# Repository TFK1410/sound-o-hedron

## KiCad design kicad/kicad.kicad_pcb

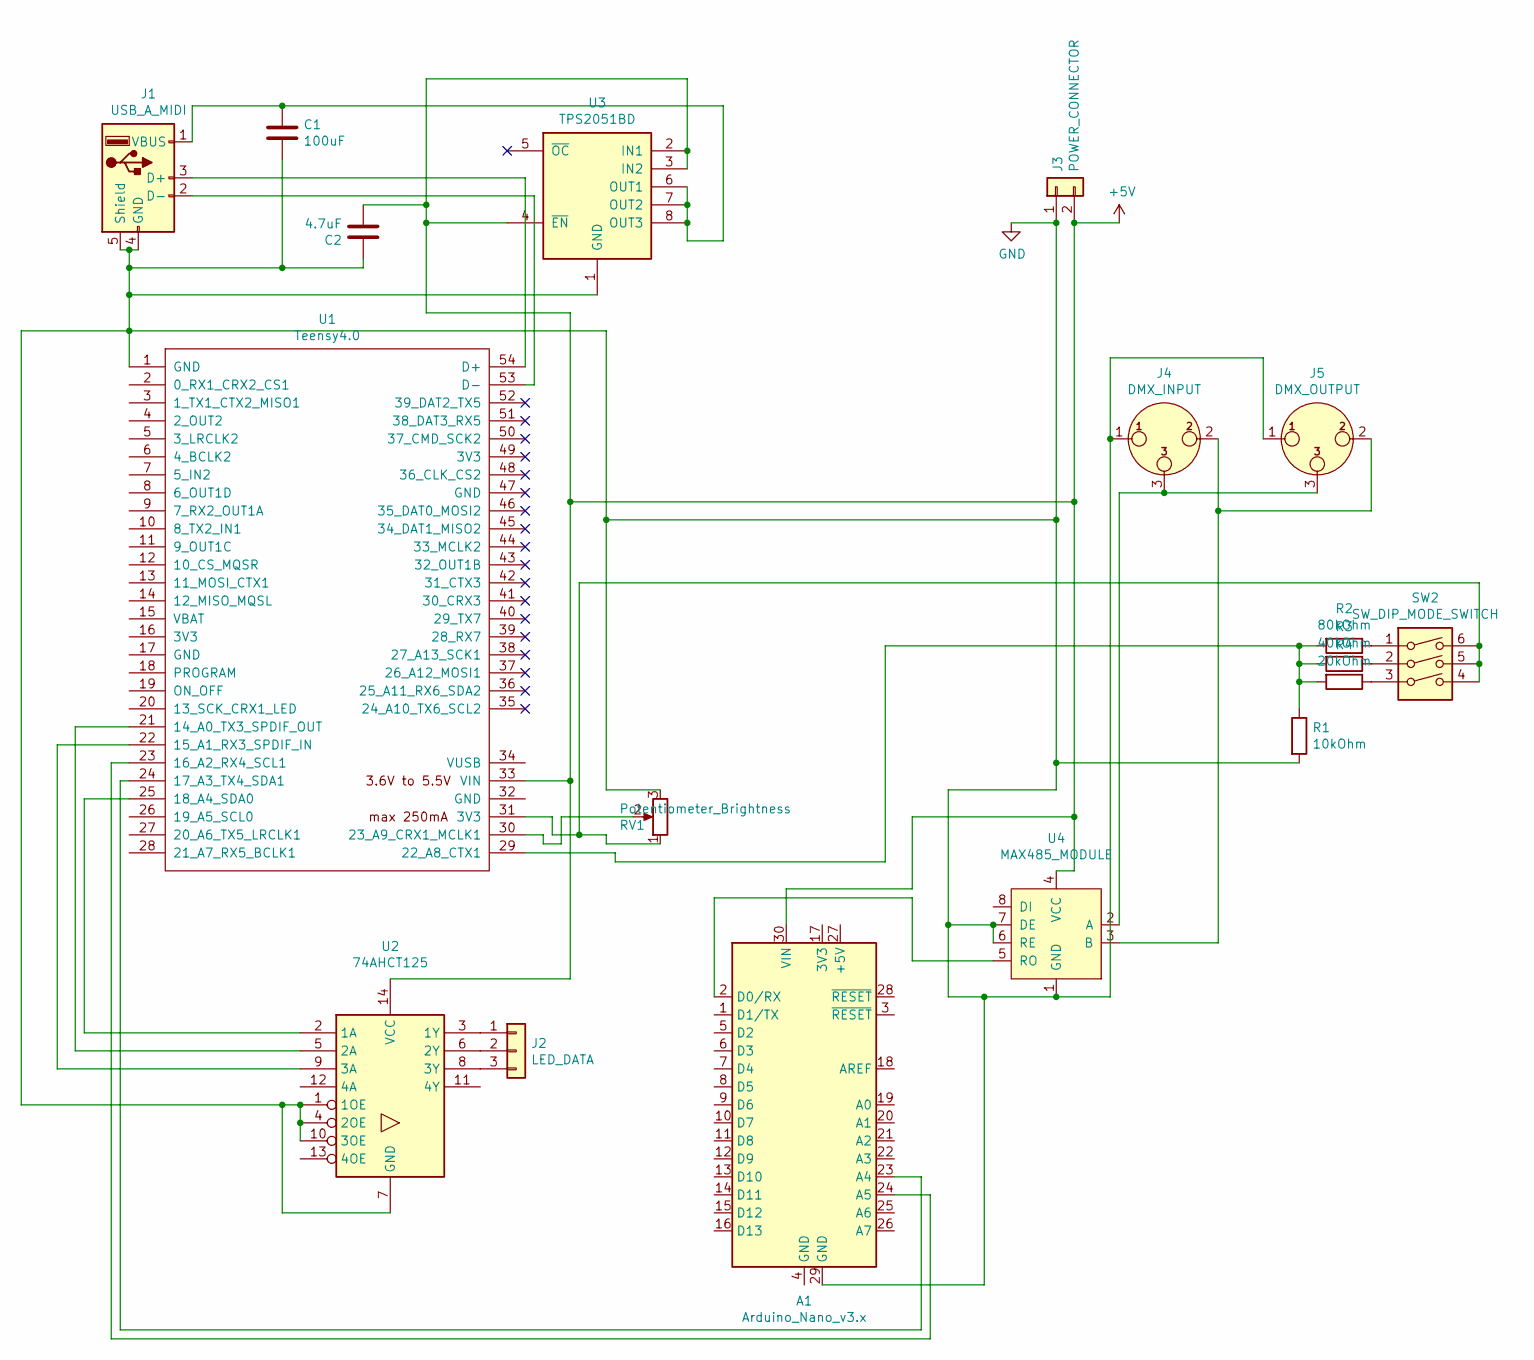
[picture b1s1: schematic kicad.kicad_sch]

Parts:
A1: Arduino_Nano_v3.x; Arduino_Nano
C1: 100uF; CP_Radial_D8.0mm_P3.50mm
C2: 4.7uF; CP_Radial_D5.0mm_P2.00mm
J1: USB_A_MIDI; PinHeader_1x05_P2.54mm_Vertical
J2: LED_DATA; PinHeader_1x03_P2.54mm_Vertical
J3: POWER_CONNECTOR; PinHeader_1x02_P2.54mm_Vertical
J4: DMX_INPUT; PinHeader_1x03_P2.54mm_Vertical
J5: DMX_OUTPUT; PinHeader_1x03_P2.54mm_Vertical
R1: 10kOhm; R_Axial_DIN0207_L6.3mm_D2.5mm_P7.62mm_Horizontal
R2: 80kOhm; R_Axial_DIN0207_L6.3mm_D2.5mm_P7.62mm_Horizontal
R3: 40kOhm; R_Axial_DIN0207_L6.3mm_D2.5mm_P7.62mm_Horizontal
R4: 20kOhm; R_Axial_DIN0207_L6.3mm_D2.5mm_P7.62mm_Horizontal
RV1: Potentiometer_Brightness; PinHeader_1x03_P2.54mm_Vertical
SW2: SW_DIP_MODE_SWITCH; PinHeader_2x03_P2.54mm_Vertical
U1: Teensy4.0; Teensy40_SMT
U2: 74AHCT125; SOIC-14_3.9x8.7mm_P1.27mm
U3: TPS2051BD; SOIC-8_3.9x4.9mm_P1.27mm
U4: MAX485_MODULE; DIP-8_MAX485_MODULE

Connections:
+5V: A1.30 (VIN), C2.1, J3.2, U1.33 (VIN), U2.14 (VCC), U3.2 (IN1), U3.3 (IN2), U3.4 (~EN), U4.4 (VCC)
GND: A1.29 (GND), C1.2, C2.2, J1.4 (GND), J1.5 (Shield), J3.1, J4.1, J5.1, R1.2, RV1.3, U1.1 (GND), U2.1 (1OE), U2.4 (2OE), U2.7 (GND), U2.10 (3OE), U3.1 (GND), U4.1 (GND), U4.6 (RE), U4.7 (DE)
unnamed: A1.2 (D0/RX), U4.5 (RO)
unnamed: A1.23 (A4), U1.24 (17_A3_TX4_SDA1)
unnamed: A1.24 (A5), U1.23 (16_A2_RX4_SCL1)
unnamed: C1.1, J1.1 (VBUS), U3.6 (OUT1), U3.7 (OUT2), U3.8 (OUT3)
unnamed: J1.2 (D-), U1.53 (D-)
unnamed: J1.3 (D+), U1.54 (D+)
unnamed: J2.1, U2.3 (1Y)
unnamed: J2.2, U2.6 (2Y)
unnamed: J2.3, U2.8 (3Y)
unnamed: J4.2, J5.2, U4.3 (B)
unnamed: J4.3, J5.3, U4.2 (A)
unnamed: R1.1, R2.2, R3.2, R4.2, U1.29 (22_A8_CTX1)
unnamed: R2.1, SW2.1
unnamed: R3.1, SW2.2
unnamed: R4.1, SW2.3
unnamed: RV1.1, SW2.4, SW2.5, SW2.6, U1.31 (3V3)
unnamed: RV1.2, U1.30 (23_A9_CRX1_MCLK1)
unnamed: U1.21 (14_A0_TX3_SPDIF_OUT), U2.5 (2A)
unnamed: U1.22 (15_A1_RX3_SPDIF_IN), U2.9 (3A)
unnamed: U1.25 (18_A4_SDA0), U2.2 (1A)

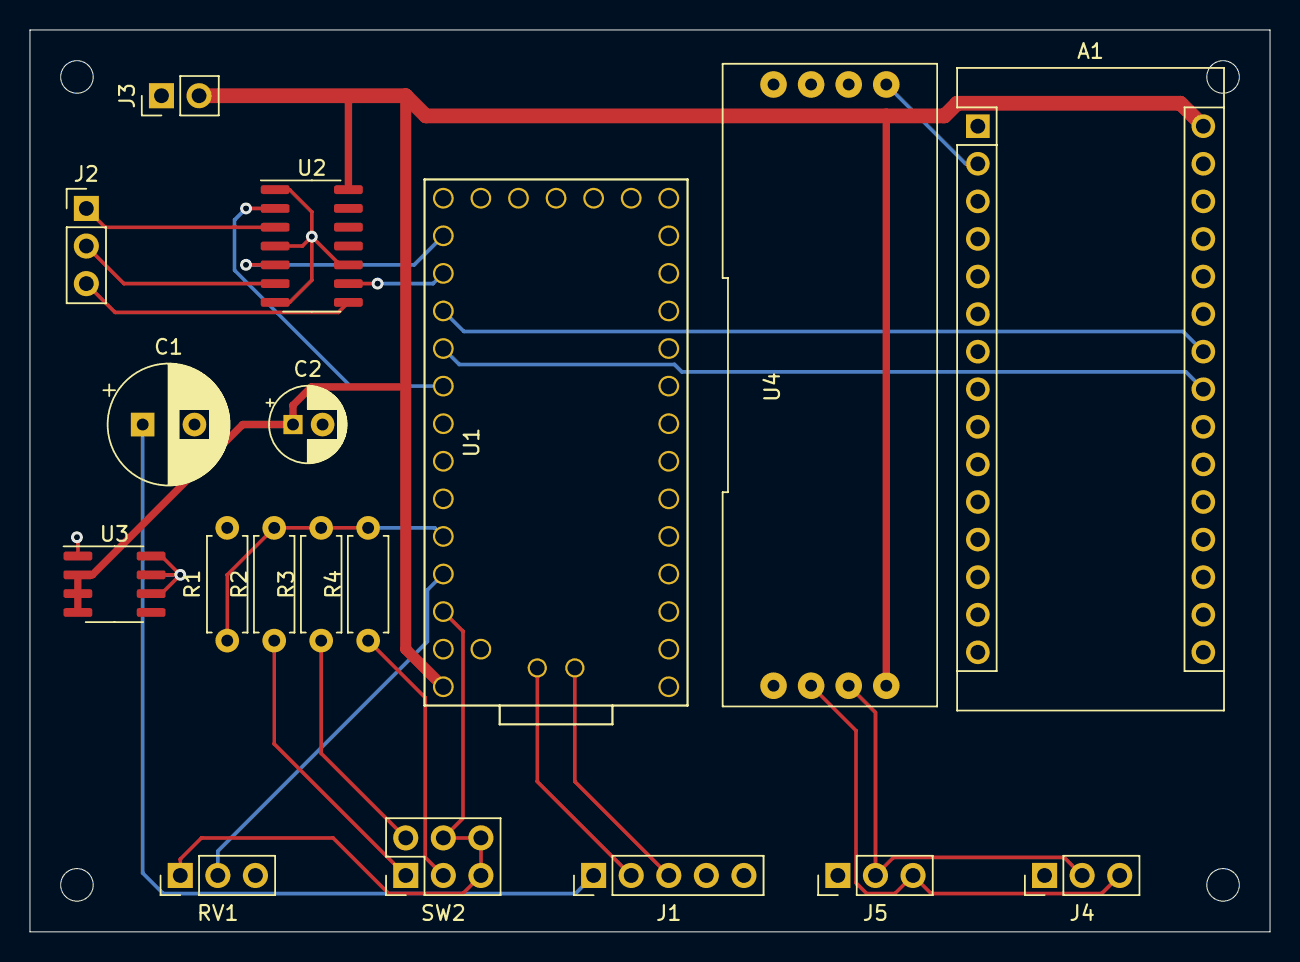
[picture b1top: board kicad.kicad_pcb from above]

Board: 2 copper layers, 83.8 x 61.0 mm, 18 parts (0 on the bottom side), 22 nets.

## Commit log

2020-07-08 Initial commit with sketches for both Teensy and Nano
2020-07-08 Small updates to the efficiency of the I2c calls
2020-07-16 First few updates using more of the features from the FastLED library
2020-07-23 Coded the edges to faces
2020-07-26 Created the basic flash effect
2020-10-17 Significant update after long hiatus
2020-10-22 Started working on impulse mode
2020-10-23 Created the simple strobe effect
2020-10-24 Created the marching line module
2020-10-27 Created the blinking pattern
2020-10-28 Added Ripple and Ghosting effects
2020-10-29 Created the fill function along with some bugfixes
2021-01-03 Added marching replicated pattern, Added pattern selection module, Minor fixes
2021-01-03 Created the DMX mode, need to test it next time
2021-01-13 Bugfixes with the DMX mode
2021-01-18 Bugfix day
2021-01-18 Teeny fix
2021-01-18 More tiny fixes
2021-04-07 Reworked the structure a bit, added a new struct, added a new pattern, added a new dmx channel for front face
2021-04-15 Fixes to some of the timing related patterns + flash pattern rework
2021-06-26 Added midi mode for the launchpad
2022-08-21 Various fixes + a mod for the 400 led num missing
2022-08-21 Updated the temp fix to a single memmove, this still has to be fixed manually as the very last LED still doesn't display anything
2023-10-30 Update to the nano receiver code and the teensy code after fixing the second chain in the dodecahedron, also updated Arduino IDE which pointed to some warnings in the MIDI module which might be the r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
2024-01-18 PicoAudio first commit
2024-01-18 To test the new approach of a dma channel ring and no smoothing on the pico side
2024-01-18 Removed some comments
2024-01-18 Removed the copyright as it is not valid
2024-01-25 Added picoprobe configuration, reworked the audio recording loop to be purely based around dma channels in chain
